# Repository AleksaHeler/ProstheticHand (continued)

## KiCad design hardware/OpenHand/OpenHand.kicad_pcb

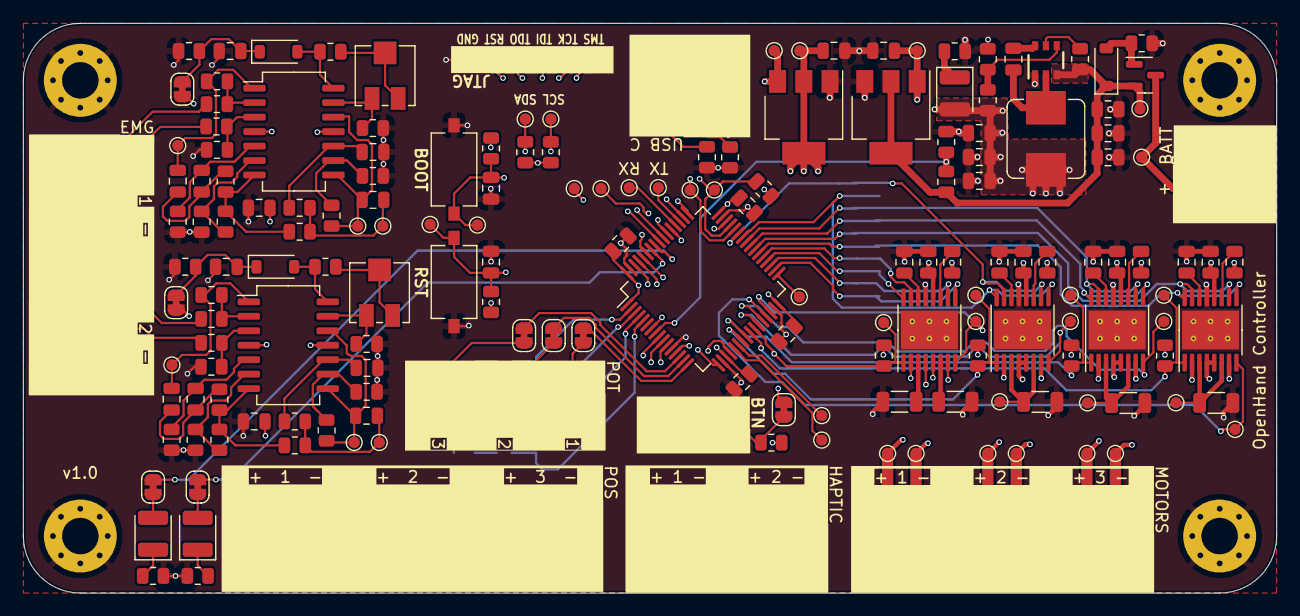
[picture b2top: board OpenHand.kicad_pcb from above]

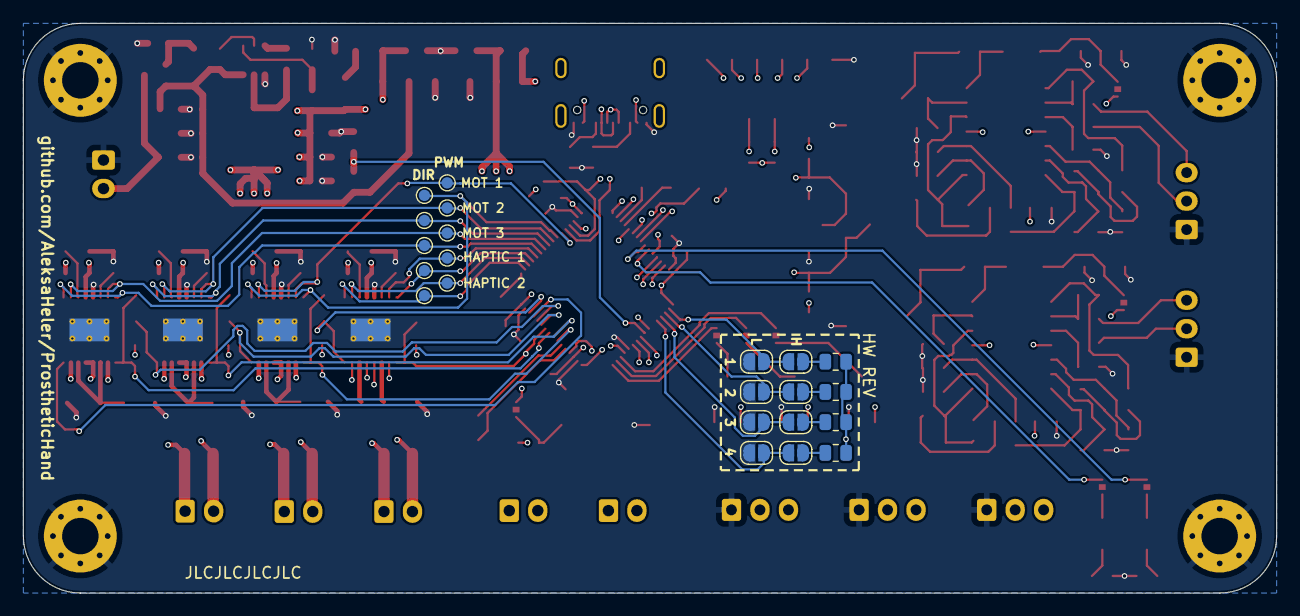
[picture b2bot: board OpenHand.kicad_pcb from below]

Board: 4 copper layers, 110.0 x 50.0 mm, 214 parts (22 on the bottom side), 135 nets.

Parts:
C1, C2, C3, C4, C5, C6, C9, C10, C16, C17: 100n; C_0805_2012Metric
C7, C8, C26, C27, C32, C33, C38, C39: 10u; C_0805_2012Metric
C11, C12, C14, C15: 22u; C_0805_2012Metric
C13: 1u; C_0805_2012Metric
C18, C19, C20, C21, C22, C23: 470n; C_0805_2012Metric
C24, C25: 330n; C_0805_2012Metric
C28, C29, C34, C35: 2u2; C_0805_2012Metric
C30, C31, C36, C37: 10n; C_0805_2012Metric
D1, D4: RED; LED_1210_3225Metric
D2: GREEN; LED_1210_3225Metric
D3: 5V Zener; D_SOD-123
D5, D6: SS14; D_SOD-123
H1, H2, H3, H4: M3_Hole; MountingHole_3.2mm_M3_Pad_Via
J1: CONN_MOTOR_1; JST_EH_S2B-EH_1x02_P2.50mm_Horizontal
J2: CONN_MOTOR_2; JST_EH_S2B-EH_1x02_P2.50mm_Horizontal
J3: CONN_BATT; JST_EH_S2B-EH_1x02_P2.50mm_Horizontal
J4: CONN_POS_1; JST_EH_S3B-EH_1x03_P2.50mm_Horizontal
J5: USB_C_CONN; USB_C_Receptacle_G-Switch_GT-USB-7010ASV
J6: CONN_MOTOR_3; JST_EH_S2B-EH_1x02_P2.50mm_Horizontal
J7: CONN_FDBK_1; JST_EH_S2B-EH_1x02_P2.50mm_Horizontal
J8: CONN_EMG_1; JST_EH_S3B-EH_1x03_P2.50mm_Horizontal
J9: CONN_POS_2; JST_EH_S3B-EH_1x03_P2.50mm_Horizontal
J10: CONN_FDBK_2; JST_EH_S2B-EH_1x02_P2.50mm_Horizontal
J11: CONN_EMG_2; JST_EH_S3B-EH_1x03_P2.50mm_Horizontal
J12: CONN_POS_3; JST_EH_S3B-EH_1x03_P2.50mm_Horizontal
JP1: JMPR_TRIM_1; SolderJumper-2_P1.3mm_Bridged_RoundedPad1.0x1.5mm
JP2: JMPR_LED_1; SolderJumper-2_P1.3mm_Bridged_RoundedPad1.0x1.5mm
JP3: JMPR_BTN_1; SolderJumper-2_P1.3mm_Bridged_RoundedPad1.0x1.5mm
JP4: JMPR_LED_2; SolderJumper-2_P1.3mm_Bridged_RoundedPad1.0x1.5mm
JP5: JMPR_TRIM_2; SolderJumper-2_P1.3mm_Bridged_RoundedPad1.0x1.5mm
JP6: JMPR_POT_1; SolderJumper-2_P1.3mm_Bridged_RoundedPad1.0x1.5mm
JP7, JP8, JP9, JP10, JP11, JP12, JP13, JP14: SolderJumper_2_Open; SolderJumper-2_P1.3mm_Open_RoundedPad1.0x1.5mm
JP15: JMPR_EMG_1_UC; SolderJumper-2_P1.3mm_Bridged_RoundedPad1.0x1.5mm
JP16: JMPR_EMG_2_UC; SolderJumper-2_P1.3mm_Bridged_RoundedPad1.0x1.5mm
L1: 3.3uH; L_Bourns_SRP7028A_7.3x6.6mm
Q1: AO3401A; SOT-23
R1, R5, R6, R7, R8, R12, R13, R14, R15, R16, R17, R21, R34, R37, R46, R47, R52, R53, R56, R57: 10k; R_0805_2012Metric
R2, R3: 5k1; R_0805_2012Metric
R4: 1.5k; R_0805_2012Metric
R9, R10, R20: 4k7; R_0805_2012Metric
R11, R19, R22, R24, R32, R35, R42, R43: 47k; R_0805_2012Metric
R18: 54.9k; R_0805_2012Metric
R23, R25, R33, R36: 15k; R_0805_2012Metric
R26, R27, R28, R29, R30, R31, R40, R41, R44, R45: 1k; R_0805_2012Metric
R38, R39, R48, R49, R50, R51: 18k; R_0805_2012Metric
R54, R55, R59: 0R2; R_1206_3216Metric
R58, R60: 4R7; R_1206_3216Metric
RV1: TRIM_POT_1; Potentiometer_Vishay_TS53YJ_Vertical
RV2: TRIM_POT_2; Potentiometer_Vishay_TS53YJ_Vertical
RV3: TRIM_POT_3; Potentiometer_Vishay_TS53YJ_Vertical
RV4, RV5: 100k; Potentiometer_Vishay_TS53YJ_Vertical
SW1: BTN_RST; SW_Tactile_SPST_NO_Straight_CK_PTS636Sx25SMTRLFS
SW2: BTN_BOOT; SW_Tactile_SPST_NO_Straight_CK_PTS636Sx25SMTRLFS
SW3: SW_Push; SW_Tactile_SPST_NO_Straight_CK_PTS636Sx25SMTRLFS
TP1: TP_BTN_RST; TestPoint_Pad_D1.0mm
TP2: TP_USB_D_P; TestPoint_Pad_D1.0mm
TP3: TP_USB_D_N; TestPoint_Pad_D1.0mm
TP4: TP_BTN_BOOT; TestPoint_Pad_D1.0mm
TP5: TP_JTAG_TMS; TestPoint_Pad_D1.0mm
TP6: TP_JTAG_TCK; TestPoint_Pad_D1.0mm
TP7: TP_JTAG_TDI; TestPoint_Pad_D1.0mm
TP8: TP_JTAG_TDO; TestPoint_Pad_D1.0mm
TP9: TP_JTAG_RST; TestPoint_Pad_D1.0mm
TP10: TP_JTAG_GND; TestPoint_Pad_D1.0mm
TP12: TP_UC_PIN_PA5; TestPoint_Pad_D1.0mm
TP13: TP_UC_PIN_PD2; TestPoint_Pad_D1.0mm
TP14: TP_UC_PIN_PA6; TestPoint_Pad_D1.0mm
TP18: TP_UC_TX; TestPoint_Pad_D1.0mm
TP19: TP_UC_RX; TestPoint_Pad_D1.0mm
TP20: TP_UC_PIN_PC12; TestPoint_Pad_D1.0mm
TP21: TP_UC_SCL; TestPoint_Pad_D1.0mm
TP22: TP_UC_SDA; TestPoint_Pad_D1.0mm
TP23: TP_UC_PIN_PB12; TestPoint_Pad_D1.0mm
TP24: TP_BATT_P; TestPoint_Pad_D1.0mm
TP25: TP_V_BATT; TestPoint_Pad_D1.0mm
TP26: TP_V_5V; TestPoint_Pad_D1.0mm
TP27: TP_V_3V3; TestPoint_Pad_D1.0mm
TP28: TP_V_N5V; TestPoint_Pad_D1.0mm
TP29: TP_EMG_1_AMP; TestPoint_Pad_D1.0mm
TP30: TP_EMG_2_AMP; TestPoint_Pad_D1.0mm
TP31: TP_EMG_1_HP; TestPoint_Pad_D1.0mm
TP32: TP_EMG_2_HP; TestPoint_Pad_D1.0mm
TP33: TP_EMG_1_LP; TestPoint_Pad_D1.0mm
TP34: TP_EMG_2_LP; TestPoint_Pad_D1.0mm
TP35: TP_MOT_1_EN; TestPoint_Pad_D1.0mm
TP36: TP_MOT_2_EN; TestPoint_Pad_D1.0mm
TP37: TP_MOT_1_IS; TestPoint_Pad_D1.0mm
TP38: TP_MOT_1_FAULT; TestPoint_Pad_D1.0mm
TP39: TP_MOT_2_IS; TestPoint_Pad_D1.0mm
TP40: TP_MOT_2_FAULT; TestPoint_Pad_D1.0mm
TP41: TP_MOT_1_UC1; TestPoint_Pad_D1.0mm
TP42: TP_MOT_2_UC1; TestPoint_Pad_D1.0mm
TP43: TP_MOT_1_UC2; TestPoint_Pad_D1.0mm
TP44: TP_MOT_2_UC2; TestPoint_Pad_D1.0mm
TP45: TP_MOT_1_OUT_P; TestPoint_Pad_D1.0mm
TP46: TP_MOT_2_OUT_P; TestPoint_Pad_D1.0mm
TP47: TP_MOT_1_OUT_N; TestPoint_Pad_D1.0mm
TP48: TP_MOT_2_OUT_N; TestPoint_Pad_D1.0mm
TP49: TP_MOT_3_EN; TestPoint_Pad_D1.0mm
TP50: TP_FDBK_MOT_EN; TestPoint_Pad_D1.0mm
TP51: TP_MOT_3_IS; TestPoint_Pad_D1.0mm
TP52: TP_MOT_3_FAULT; TestPoint_Pad_D1.0mm
TP53: TP_FDBK_MOT_FAULT; TestPoint_Pad_D1.0mm
TP54: TP_MOT_3_UC1; TestPoint_Pad_D1.0mm
TP55: TP_FDBK_MOT_1_UC1; TestPoint_Pad_D1.0mm
TP56: TP_MOT_3_UC2; TestPoint_Pad_D1.0mm
TP57: TP_FDBK_MOT_1_UC2; TestPoint_Pad_D1.0mm
TP58: TP_MOT_3_OUT_P; TestPoint_Pad_D1.0mm
TP59: TP_MOT_3_OUT_N; TestPoint_Pad_D1.0mm
TP60: TP_FDBK_MOT_2_UC1; TestPoint_Pad_D1.0mm
TP61: TP_FDBK_MOT_2_UC2; TestPoint_Pad_D1.0mm
U1: STM32F103RETx; LQFP-64_10x10mm_P0.5mm
U2: TPS565201DDCR; TPS565201DDCR_L
U3: AMS1117-3.3; SOT-223-3_TabPin2
U4: LT1175-5_SOT223; SOT-223-3_TabPin2
U5, U6: LM324; SO-14_5.3x10.2mm_P1.27mm
U7, U8, U9, U10: DRV8833PWP; HTSSOP-16-1EP_4.4x5mm_P0.65mm_EP3.4x5mm_Mask2.46x2.31mm_The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

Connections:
+3V3: C3.1, C4.1, C5.1, C6.1, C14.1, J4.3, J9.3, J12.3, R1.1, R4.2, R5.1, R6.2, R7.2, R8.1, R13.1, R14.1, R15.1, R16.1, RV1.3, RV2.3, RV3.3, TP27.1, U1.1 (VBAT), U1.13 (VDDA), U1.19 (VDD), U1.32 (VDD), U1.48 (VDD), U1.64 (VDD), U3.2 (VO)
+5V: C11.1, C12.1, C13.1, C16.1, C17.1, C30.1, C31.1, C32.1, C33.1, C36.1, C37.1, C38.1, C39.1, D4.2 (A), J5.A4 (VBUS), J5.A9 (VBUS), J5.B4 (VBUS), J5.B9 (VBUS), L1.2, R18.1, R52.2, R53.2, R56.2, R57.2, TP26.1, U3.3 (VI), U5.4 (V+), U6.4 (V+), U7.12 (VM), U8.12 (VM), U9.12 (VM), U10.12 (VM)
+BATT: C7.1, C8.1, C9.1, D3.1 (K), Q1.2 (S), R11.2, R17.2, TP25.1, U2.3 (VIN), U4.2 (IN)
-5V: C15.1, TP28.1, U4.1 (OUT), U5.11 (V-), U6.11 (V-)
/BATT_SENSE: R11.1, R12.2, U1.8 (PC0)
/Sensors/amp_out_1: C18.1, R32.2, TP29.1, U5.1
BAT_P: J3.2, Q1.3 (D), TP24.1
BTN_01: JP3.2 (B), U1.59 (PB7)
EMG_1_MIDPOINT: C22.1, R29.2, R40.1, TP31.1
EMG_01_N: J8.3, R28.2
EMG_01_P: J8.2, R26.2
EMG_01_UC: JP15.2 (B), U1.17 (PA3)
EMG_2_MIDPOINT: C23.1, R31.2, R41.1, TP32.1
EMG_02_N: J11.3, R30.2
EMG_02_P: J11.2, R27.2
EMG_02_UC: JP16.2 (B), U1.20 (PA4)
Earth: C1.2, C2.2, C3.2, C4.2, C5.2, C6.2, C7.2, C8.2, C9.2, C11.2, C12.2, C13.2, C14.2, C15.2, C16.2, C17.2, C24.1, C25.1, C26.2, C27.2, C28.1, C29.1, C32.2, C33.2, C34.1, C35.1, C38.2, C39.2, H1.1, H2.1, H3.1, H4.1, J3.1, J4.1, J5.A1 (GND), J5.A12 (GND), J5.B1 (GND), J5.B12 (GND), J8.1, J9.1, J11.1, J12.1, JP11.1 (A), JP12.1 (A), JP13.1 (A), JP14.1 (A), R2.2, R3.2, R9.2, R10.2, R12.1, R19.1, R20.2, R21.2, R22.1, R24.1, R33.2, R36.2, R38.2, R39.2, R44.2, R45.2, R48.2, R49.2, R50.2, R51.2, R54.1, R55.1, R58.1, R59.1, R60.1, RV1.1, RV2.1, RV3.1, SW1.2, SW2.2, SW3.2, TP10.1, U1.12 (VSSA), U1.18 (VSS), U1.31 (VSS), U1.47 (VSS), U1.63 (VSS), U2.1 (GND), U3.1 (GND), U4.3 (GND), U7.13 (GND), U7.17 (GND(PPAD)), U8.13 (GND), U8.17 (GND(PPAD)), U9.13 (GND), U9.17 (GND(PPAD)), U10.13 (GND), U10.17 (GND(PPAD))
HALL_SENS_01_S: J4.2, U1.9 (PC1)
HALL_SENS_02_S: J9.2, U1.10 (PC2)
HALL_SENS_03_S: J12.2, U1.11 (PC3)
HAPTIC_01_DIR: TP55.1, U1.36 (PB15), U10.16 (AIN1)
HAPTIC_01_N: J7.1, U10.4 (AOUT2)
HAPTIC_01_P: J7.2, U10.2 (AOUT1)
HAPTIC_01_PWM: TP57.1, U1.37 (PC6), U10.15 (AIN2)
HAPTIC_02_DIR: TP60.1, U1.34 (PB13), U10.9 (BIN1)
HAPTIC_02_N: J10.1, U10.5 (BOUT2)
HAPTIC_02_P: J10.2, U10.7 (BOUT1)
HAPTIC_02_PWM: TP61.1, U1.35 (PB14), U10.10 (BIN2)
HAPTIC_EN: R57.1, TP50.1, U1.26 (PB0), U10.1 (nSLEEP)
HAPTIC_FAULT: TP53.1, U1.30 (PB11), U10.8 (nFAULT)
HW_REV_01: JP7.1 (A), JP11.2 (B), U1.2 (PC13)
HW_REV_02: JP8.1 (A), JP12.2 (B), U1.3 (PC14)
HW_REV_03: JP9.1 (A), JP13.2 (B), U1.4 (PC15)
HW_REV_04: JP10.1 (A), JP14.2 (B), U1.5 (PD0)
JTAG_RST: TP9.1, U1.56 (PB4)
JTAG_TCK: TP6.1, U1.49 (PA14)
JTAG_TDI: TP7.1, U1.50 (PA15)
JTAG_TDO: TP8.1, U1.55 (PB3)
JTAG_TMS: TP5.1, U1.46 (PA13)
LED_1: JP2.2 (B), U1.57 (PB5)
LED_2: JP4.2 (B), U1.58 (PB6)
MOTOR_01_DIR: TP41.1, U1.42 (PA9), U7.9 (BIN1), U7.16 (AIN1)
MOTOR_01_EN: R52.1, TP35.1, U1.23 (PA7), U7.1 (nSLEEP)
MOTOR_01_FAULT: TP38.1, U1.27 (PB1), U7.8 (nFAULT)
MOTOR_01_N: J1.1, TP47.1, U7.4 (AOUT2), U7.5 (BOUT2)
MOTOR_01_P: J1.2, TP45.1, U7.2 (AOUT1), U7.7 (BOUT1)
MOTOR_01_PWM: TP43.1, U1.43 (PA10), U7.10 (BIN2), U7.15 (AIN2)
MOTOR_02_DIR: TP42.1, U1.40 (PC9), U8.9 (BIN1), U8.16 (AIN1)
MOTOR_02_EN: R53.1, TP36.1, U1.24 (PC4), U8.1 (nSLEEP)
MOTOR_02_FAULT: TP40.1, U1.28 (PB2), U8.8 (nFAULT)
MOTOR_02_N: J2.1, TP48.1, U8.4 (AOUT2), U8.5 (BOUT2)
MOTOR_02_P: J2.2, TP46.1, U8.2 (AOUT1), U8.7 (BOUT1)
MOTOR_02_PWM: TP44.1, U1.41 (PA8), U8.10 (BIN2), U8.15 (AIN2)
MOTOR_03_DIR: TP54.1, U1.38 (PC7), U9.9 (BIN1), U9.16 (AIN1)
MOTOR_03_EN: R56.1, TP49.1, U1.25 (PC5), U9.1 (nSLEEP)
MOTOR_03_FAULT: TP52.1, U1.29 (PB10), U9.8 (nFAULT)
MOTOR_03_N: J6.1, TP59.1, U9.4 (AOUT2), U9.5 (BOUT2)
MOTOR_03_P: J6.2, TP58.1, U9.2 (AOUT1), U9.7 (BOUT1)
MOTOR_03_PWM: TP56.1, U1.39 (PC8), U9.10 (BIN2), U9.15 (AIN2)
unnamed: C18.2, C19.1, R23.1
unnamed: C20.1, R35.2, TP30.1, U6.1
unnamed: C20.2, C21.1, R25.1
unnamed: D1.2 (A), JP2.1 (A)
unnamed: D1.1 (K), R9.1
unnamed: D2.2 (A), JP4.1 (A)
unnamed: D2.1 (K), R10.1
unnamed: D3.2 (A), Q1.1 (G), R19.2
unnamed: D4.1 (K), R20.1
unnamed: D5.2 (A), R43.1, U5.14
unnamed: C26.1, D5.1 (K), JP15.1 (A), R48.1
unnamed: D6.2 (A), R42.1, U6.14
unnamed: C27.1, D6.1 (K), JP16.1 (A), R51.1
unnamed: J5.A5 (CC1), R2.1
unnamed: J5.B5 (CC2), R3.1
unnamed: JP1.1 (A), RV1.2
unnamed: JP3.1 (A), R8.2, SW3.1
unnamed: JP5.1 (A), RV2.2
unnamed: JP6.1 (A), RV3.2
unnamed: JP7.2 (B), R13.2
unnamed: JP8.2 (B), R14.2
unnamed: JP9.2 (B), R15.2
unnamed: JP10.2 (B), R16.2
unnamed: R23.2, R29.1, R34.2, U5.7
unnamed: R25.2, R31.1, R37.2, U6.7
unnamed: R42.2, RV5.1, RV5.2
unnamed: R43.2, RV4.1, RV4.2
unnamed: TP12.1, U1.21 (PA5)
unnamed: TP14.1, U1.22 (PA6)
unnamed: TP23.1, U1.33 (PB12)
unnamed: TP20.1, U1.53 (PC12)
unnamed: TP13.1, U1.54 (PD2)
unnamed: R17.1, U2.5 (EN)
unnamed: C10.1, L1.1, U2.2 (SW)
unnamed: C10.2, U2.6 (VBST)
unnamed: R18.2, R21.1, U2.4 (VFB)
unnamed: R22.2, R26.1, U5.3 (+)
unnamed: R28.1, R32.1, U5.2 (-)
unnamed: C19.2, R33.1, U5.5 (+)
unnamed: R34.1, R38.1, U5.6 (-)
unnamed: C24.2, R40.2, U5.10 (+)
unnamed: R46.1, R49.1, U5.9 (-)
unnamed: C22.2, R46.2, TP33.1, U5.8, U5.12 (+)
unnamed: R44.1, RV4.3, U5.13 (-)
unnamed: R24.2, R27.1, U6.3 (+)
unnamed: R30.1, R35.1, U6.2 (-)
unnamed: C21.2, R36.1, U6.5 (+)
unnamed: R37.1, R39.1, U6.6 (-)
unnamed: C25.2, R41.2, U6.10 (+)
unnamed: R47.1, R50.1, U6.9 (-)
unnamed: C23.2, R47.2, TP34.1, U6.8, U6.12 (+)
unnamed: R45.1, RV5.3, U6.13 (-)
unnamed: R54.2, TP37.1, U7.3 (AISEN), U7.6 (BISEN)
unnamed: C30.2, U7.11 (VCP)
unnamed: C28.2, U7.14 (VINT)
unnamed: R55.2, TP39.1, U8.3 (AISEN), U8.6 (BISEN)
unnamed: C31.2, U8.11 (VCP)
unnamed: C29.2, U8.14 (VINT)
unnamed: R59.2, TP51.1, U9.3 (AISEN), U9.6 (BISEN)
unnamed: C36.2, U9.11 (VCP)
unnamed: C34.2, U9.14 (VINT)
unnamed: R58.2, U10.3 (AISEN)
unnamed: R60.2, U10.6 (BISEN)
unnamed: C37.2, U10.11 (VCP)
unnamed: C35.2, U10.14 (VINT)
TRIM_POT_01: JP1.2 (B), U1.16 (PA2)
TRIM_POT_02: JP5.2 (B), U1.15 (PA1)
TRIM_POT_03: JP6.2 (B), U1.14 (PA0)
UC_BOOT: C2.1, R5.2, SW2.1, TP4.1, U1.60 (BOOT0)
UC_RST: C1.1, R1.2, SW1.1, TP1.1, U1.7 (NRST)
UC_RX: TP19.1, U1.52 (PC11)
UC_SCL: R7.1, TP21.1, U1.61 (PB8)
UC_SDA: R6.1, TP22.1, U1.62 (PB9)
UC_TX: TP18.1, U1.51 (PC10)
USB_D+: J5.A7 (D-), J5.B7 (D-), R4.1, TP2.1, U1.45 (PA12)
USB_D-: J5.A6 (D+), J5.B6 (D+), TP3.1, U1.44 (PA11)

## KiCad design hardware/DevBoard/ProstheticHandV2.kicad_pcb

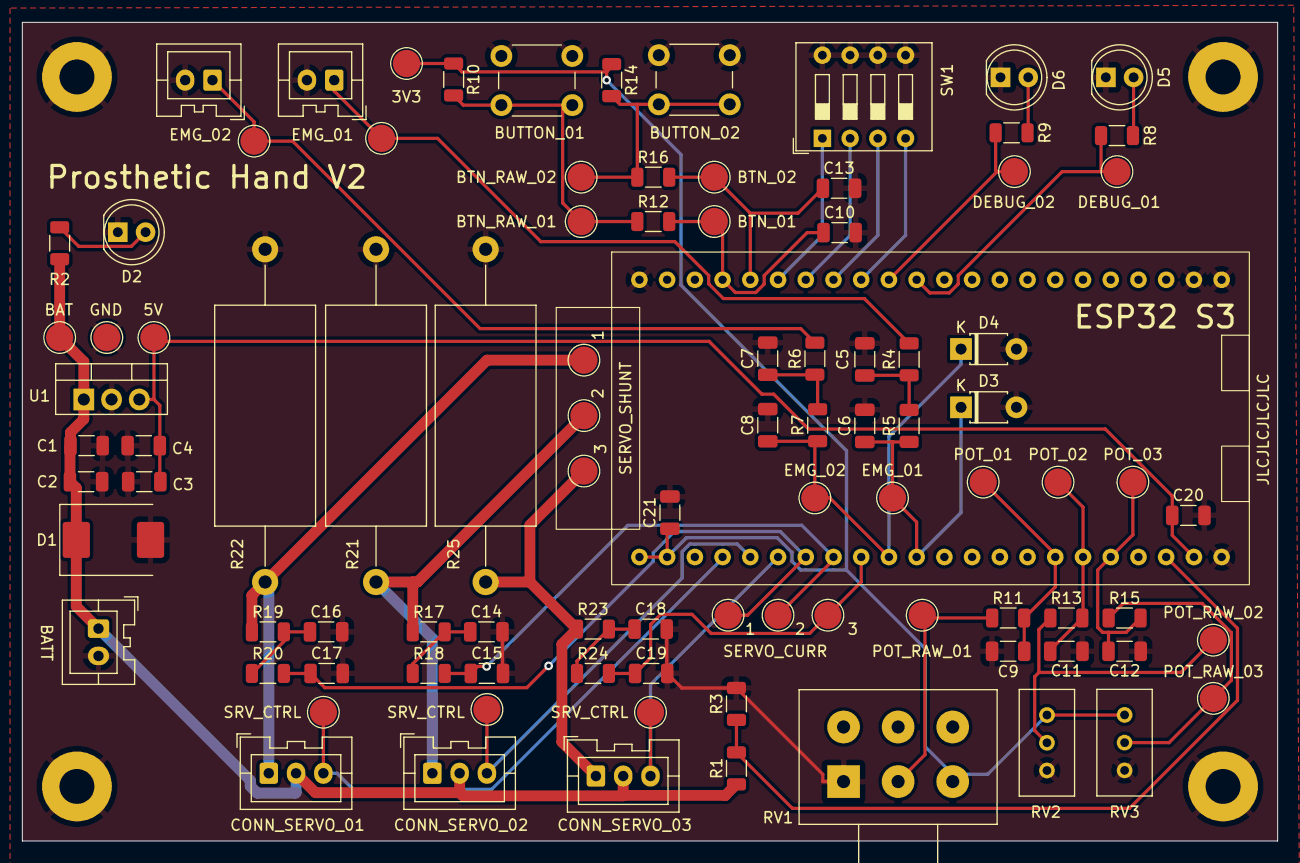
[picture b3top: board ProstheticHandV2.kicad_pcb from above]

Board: 2 copper layers, 115.0 x 75.0 mm, 99 parts (0 on the bottom side), 42 nets.

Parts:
A1: ESP32S3_DevModule
C1, C3, C5, C6, C7, C8: 1uF; C_1206_3216Metric
C2, C4, C9, C10, C11, C12, C13, C20, C21: 0.1uF; C_1206_3216Metric
C14, C15, C16, C17, C18, C19: 100nF; C_1206_3216Metric
D1: SK36; D_SMC
D2: LED GREEN; LED_D5.0mm
D3, D4: 5v1; D_T-1_P5.08mm_Horizontal
D5: LED RED; LED_D5.0mm
D6: LED BLUE; LED_D5.0mm
H1, H2, H3, H4: MountingHole_Pad; MountingHole_3.2mm_M3_Pad
J1: BATT_CONNECTOR; JST_XA_B02B-XASK-1_1x02_P2.50mm_Vertical
J2: EMG_SENSOR_01; JST_XA_B02B-XASK-1_1x02_P2.50mm_Vertical
J3: EMG_SENSOR_02; JST_XA_B02B-XASK-1_1x02_P2.50mm_Vertical
J4: CONN_SERVO_02; JST_XA_B03B-XASK-1_1x03_P2.50mm_Vertical
J5: CONN_SERVO_01; JST_XA_B03B-XASK-1_1x03_P2.50mm_Vertical
J6: CONN_SERVO_03; JST_XA_B03B-XASK-1_1x03_P2.50mm_Vertical
R1: 4k7; R_1206_3216Metric
R2, R4, R5, R6, R7, R10, R11, R12, R13, R14, R15, R16: 10k; R_1206_3216Metric
R3, R17, R18, R19, R20, R23, R24: 1k; R_1206_3216Metric
R8, R9: 220; R_1206_3216Metric
R21, R22, R25: 0.1; R_Axial_DIN0922_L20.0mm_D9.0mm_P30.48mm_Horizontal
RV1: Pot. 5k; Potentiometer_Alps_RK163_Dual_Horizontal
RV2, RV3: Trim Pot. 10k; Potentiometer_Bourns_3296W_Vertical
SW1: DIP_SWITCH; SW_DIP_SPSTx04_Slide_9.78x12.34mm_W7.62mm_P2.54mm
SW2: BUTTON_01; SW_PUSH_6mm_H5mm
SW3: BUTTON_02; SW_PUSH_6mm_H5mm
TP1: TP_BATT; TestPoint_Pad_D2.5mm
TP2: TP_5V_REG; TestPoint_Pad_D2.5mm
TP3: TP_GND; TestPoint_Pad_D2.5mm
TP4: TP_EMG_01_IN; TestPoint_Pad_D2.5mm
TP5: TP_EMG_01_UC; TestPoint_Pad_D2.5mm
TP6: TP_EMG_02_IN; TestPoint_Pad_D2.5mm
TP7: TP_EMG_02_UC; TestPoint_Pad_D2.5mm
TP8: TP_DEBUG_01; TestPoint_Pad_D2.5mm
TP9: TP_DEBUG_02; TestPoint_Pad_D2.5mm
TP10: TP_3v3; TestPoint_Pad_D2.5mm
TP11: TP_POT_RAW_01; TestPoint_Pad_D2.5mm
TP12: TP_POT_01; TestPoint_Pad_D2.5mm
TP13: TP_BTN_RAW_01; TestPoint_Pad_D2.5mm
TP14: TP_BTN_01; TestPoint_Pad_D2.5mm
TP15: TP_POT_RAW_02; TestPoint_Pad_D2.5mm
TP16: TP_POT_02; TestPoint_Pad_D2.5mm
TP17: TP_POT_RAW_03; TestPoint_Pad_D2.5mm
TP18: TP_POT_03; TestPoint_Pad_D2.5mm
TP19: TP_BTN_RAW_02; TestPoint_Pad_D2.5mm
TP20: TP_BTN_02; TestPoint_Pad_D2.5mm
TP21: TP_SERVO_CONTROL_02; TestPoint_Pad_D2.5mm
TP22: TP_SERVO_CONTROL_01; TestPoint_Pad_D2.5mm
TP23: TP_SERVO_CURR_RAW_02; TestPoint_Pad_D2.5mm
TP24: TP_SERVO_CURR_02; TestPoint_Pad_D2.5mm
TP25: TP_SERVO_CURR_RAW_01; TestPoint_Pad_D2.5mm
TP26: TP_SERVO_CURR_01; TestPoint_Pad_D2.5mm
TP27: TP_SERVO_CONTROL_03; TestPoint_Pad_D2.5mm
TP28: TP_SERVO_CURR_RAW_03; TestPoint_Pad_D2.5mm
TP29: TP_SERVO_CURR_03; TestPoint_Pad_D2.5mm
U1: LM7805_TO220; TO-220-3_Vertical

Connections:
+3V3: A1.1 (3v3), A1.2 (3v3), C21.1, R10.1, R14.1, RV1.3, RV2.3, RV3.3, TP10.1
+5V: A1.21 (5v), C3.1, C4.1, C20.1, TP2.1, U1.3 (VO)
+BATT: C1.1, C2.1, D1.1 (K), J1.1, J4.2, J5.2, J6.2, R1.1, R2.1, TP1.1, U1.1 (VI)
BATT_SENSE: A1.20 (14), R1.2, R3.1
BUTTON_01: A1.41 (1), C10.1, R12.2, TP14.1
BUTTON_02: A1.40 (2), C13.1, R16.2, TP20.1
DEBUG_LED_01: A1.34 (37), R8.1, TP8.1
DEBUG_LED_02: A1.35 (38), R9.2, TP9.1
DIP_SWITCH_00: A1.39 (42), SW1.1
DIP_SWITCH_01: A1.38 (41), SW1.2
DIP_SWITCH_02: A1.37 (40), SW1.3
DIP_SWITCH_03: A1.36 (39), SW1.4
EMG_SENSOR_01: A1.11 (18), C6.1, D3.1 (K), R5.1, TP5.1
EMG_SENSOR_02: A1.10 (17), C8.1, D4.1 (K), R7.1, TP7.1
GND: A1.22 (GND), A1.23 (GND), A1.24 (GND), A1.44 (GND), C1.2, C2.2, C3.2, C4.2, C5.2, C6.2, C7.2, C8.2, C9.2, C10.2, C11.2, C12.2, C13.2, C14.2, C15.2, C16.2, C17.2, C18.2, C19.2, C20.2, C21.2, D1.2 (A), D2.1 (K), D3.2 (A), D4.2 (A), D5.1 (K), D6.1 (K), H1.1, H2.1, H3.1, H4.1, J1.2, J2.2, J3.2, R3.2, R21.2, R22.2, R25.2, RV1.1, RV2.1, RV3.1, SW1.5, SW1.6, SW1.7, SW1.8, SW2.1, SW3.1, TP3.1, U1.2 (GND)
unnamed: C5.1, R4.1, R5.2
unnamed: C7.1, R6.1, R7.2
unnamed: C14.1, R17.2, R18.1
unnamed: C16.1, R19.2, R20.1
unnamed: C18.1, R23.2, R24.1
unnamed: D2.2 (A), R2.2
unnamed: D5.2 (A), R8.2
unnamed: D6.2 (A), R9.1
unnamed: J2.1, R4.2, TP4.1
unnamed: J3.1, R6.2, TP6.1
unnamed: J4.1, R17.1, R21.1, TP23.1
unnamed: J5.1, R19.1, R22.1, TP25.1
unnamed: J6.1, R23.1, R25.1, TP28.1
unnamed: R10.2, R12.1, SW2.2, TP13.1
unnamed: R11.1, RV1.2, TP11.1
unnamed: R13.1, RV2.2, TP15.1
unnamed: R14.2, R16.1, SW3.2, TP19.1
unnamed: R15.1, RV3.2, TP17.1
POT_01: A1.16 (10), C9.1, R11.2, TP12.1
POT_02: A1.17 (11), C11.1, R13.2, TP16.1
POT_03: A1.18 (12), C12.1, R15.2, TP18.1
SERVO_CONTROL_01: A1.4, J5.3, TP22.1
SERVO_CONTROL_02: A1.5, J4.3, TP21.1
SERVO_CONTROL_03: A1.6, J6.3, TP27.1
SERVO_CURR_01: A1.7, C17.1, R20.2, TP26.1
SERVO_CURR_02: A1.8 (15), C15.1, R18.2, TP24.1
SERVO_CURR_03: A1.9 (16), C19.1, R24.2, TP29.1

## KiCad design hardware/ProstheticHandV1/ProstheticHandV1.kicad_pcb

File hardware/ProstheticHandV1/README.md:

# PCB & HW designs of the prosthetic hand project

For designing those we use [KiCAD](https://www.kicad.org/download/). Good tutorial can be found [here](https://www.youtube.com/playlist?list=PL3bNyZYHcRSUhUXUt51W6nKvxx2ORvUQB). Although it's for a bit older version of the KiCAD it is still usefull.

For now only two project are here:
 - **DevelopmentBoard** - First example board to test the KiCAD software and to try our hand at making our own PCB at home (TODO: update this document with findings once home-made pcb is done)
 - **ProstheticHand v1** - The actual PCB design that will be used in the prosthetic hand (for the first prototype), hopefully to be ordered from PCB manufacturer

Folders:
 - **images** - contains images of the PCBs and hardware
 - **libraries** - contains libraries used in KiCAD

Versioning:
 - v1.x -> first prototype, with v1.0 being the first design, and then iterating trough v1.1, v1.2...
 - v2.x -> todo

## Development Board

Here is the schematic of the development board:

It contains 4 buttons (with pullup resistors), 3 potentiometers (two trim pots, and one guitar pot), two servo connectors, JTAG connector and 12V barrel jack.

Here are some PCB screenshots:

And some photos of the protoboard build:

## Prosthetic Hand v1

We're using EPS32-S3:
 - https://api.riot-os.org/group__cpu__esp32__esp32s3.html

Components ideas for this iteration of the board:
 - debug LED
 - 2x pot
 - oled display
 - 2x buttons
 - 4x servos
 - current shunts for servo current measurement (we have 1 ohm power resistors at hand)
 - battery voltage sensing (connected to a battery -> 4 cell Li-ion)
 - [LDO voltage regulator](https://en.wikipedia.org/wiki/Low-dropout_regulator)
 - JTAG for programming and debugging
 - external power connector (selectable between this power input or the batteries by a switch)
 - two EMG sensor input pins (simple analog read)

Used ESP32 GPIO pins:
 - Servo output -> GPIO04, GPIO05, GPIO26, GPIO27 
 - Servo current sensing -> GPIO34, GPIO35, GPIO36, GPIO39
 - Debug LED -> GPIO23
 - JTAG -> GPIO12, GPIO13, GPIO14, GPIO15
 - UART -> GPIO01, GPIO03 (using built in serial to usb chip, no our connnected hardware)
 - Buttons -> GPIO18, GPIO19
 - Pots -> GPIO32, GPIO33
 - Battery voltage -> GPIO25
 - OLED display SPI com -> GPIO21, GPIO22
 - two EMG sensor input pins (simple analog read) -> 

Maybe: selectable pin functions using DIP swithces or jumper header connectors (we had some 4x DIP switches at hand so we're using them): each pin can be routed to some functionality by enabling these DIP switches. For example we can use a pin as a button input or as a pot input based on the DIP swith configuration. This is purely hardware oriented configuration and we have to then configure the code to support these changes.

## Prosthetic Hand v2

Ideas:
- 3 servo motors, current sensing for each and MOSFET to control the power/current they get
- MOSFETs controlled by op-amps, where uC gives them using PWM signal and sets the max current
- (test if PWM to DC voltage works, test if given DC voltage by uC works with op-ampto set max current) 
- 2 debug LEDs (one main RED LED, one green LED for sensor actuating)
- 5V dropdown regulator
- battery voltage sensing
- 3 potentiometers (one big, two trim pots)
- 2 buttons
- 4 dip switches for configuration
- 2 sensor connections
- sensors will be on a separate board with 2x 9V batteries
- check if we can have OLED connected to display data or just use JSON format over serial monitor and Processing
- still use full-size ESP32 S3 Devkit C boards

KiCad 7 ESP32 PCB Design Full Tutorial: https://www.youtube.com/watch?v=b-7bMl6fJio
RF + MCU PCB Design Review: https://www.youtube.com/watch?v=71bW_sKZIZw

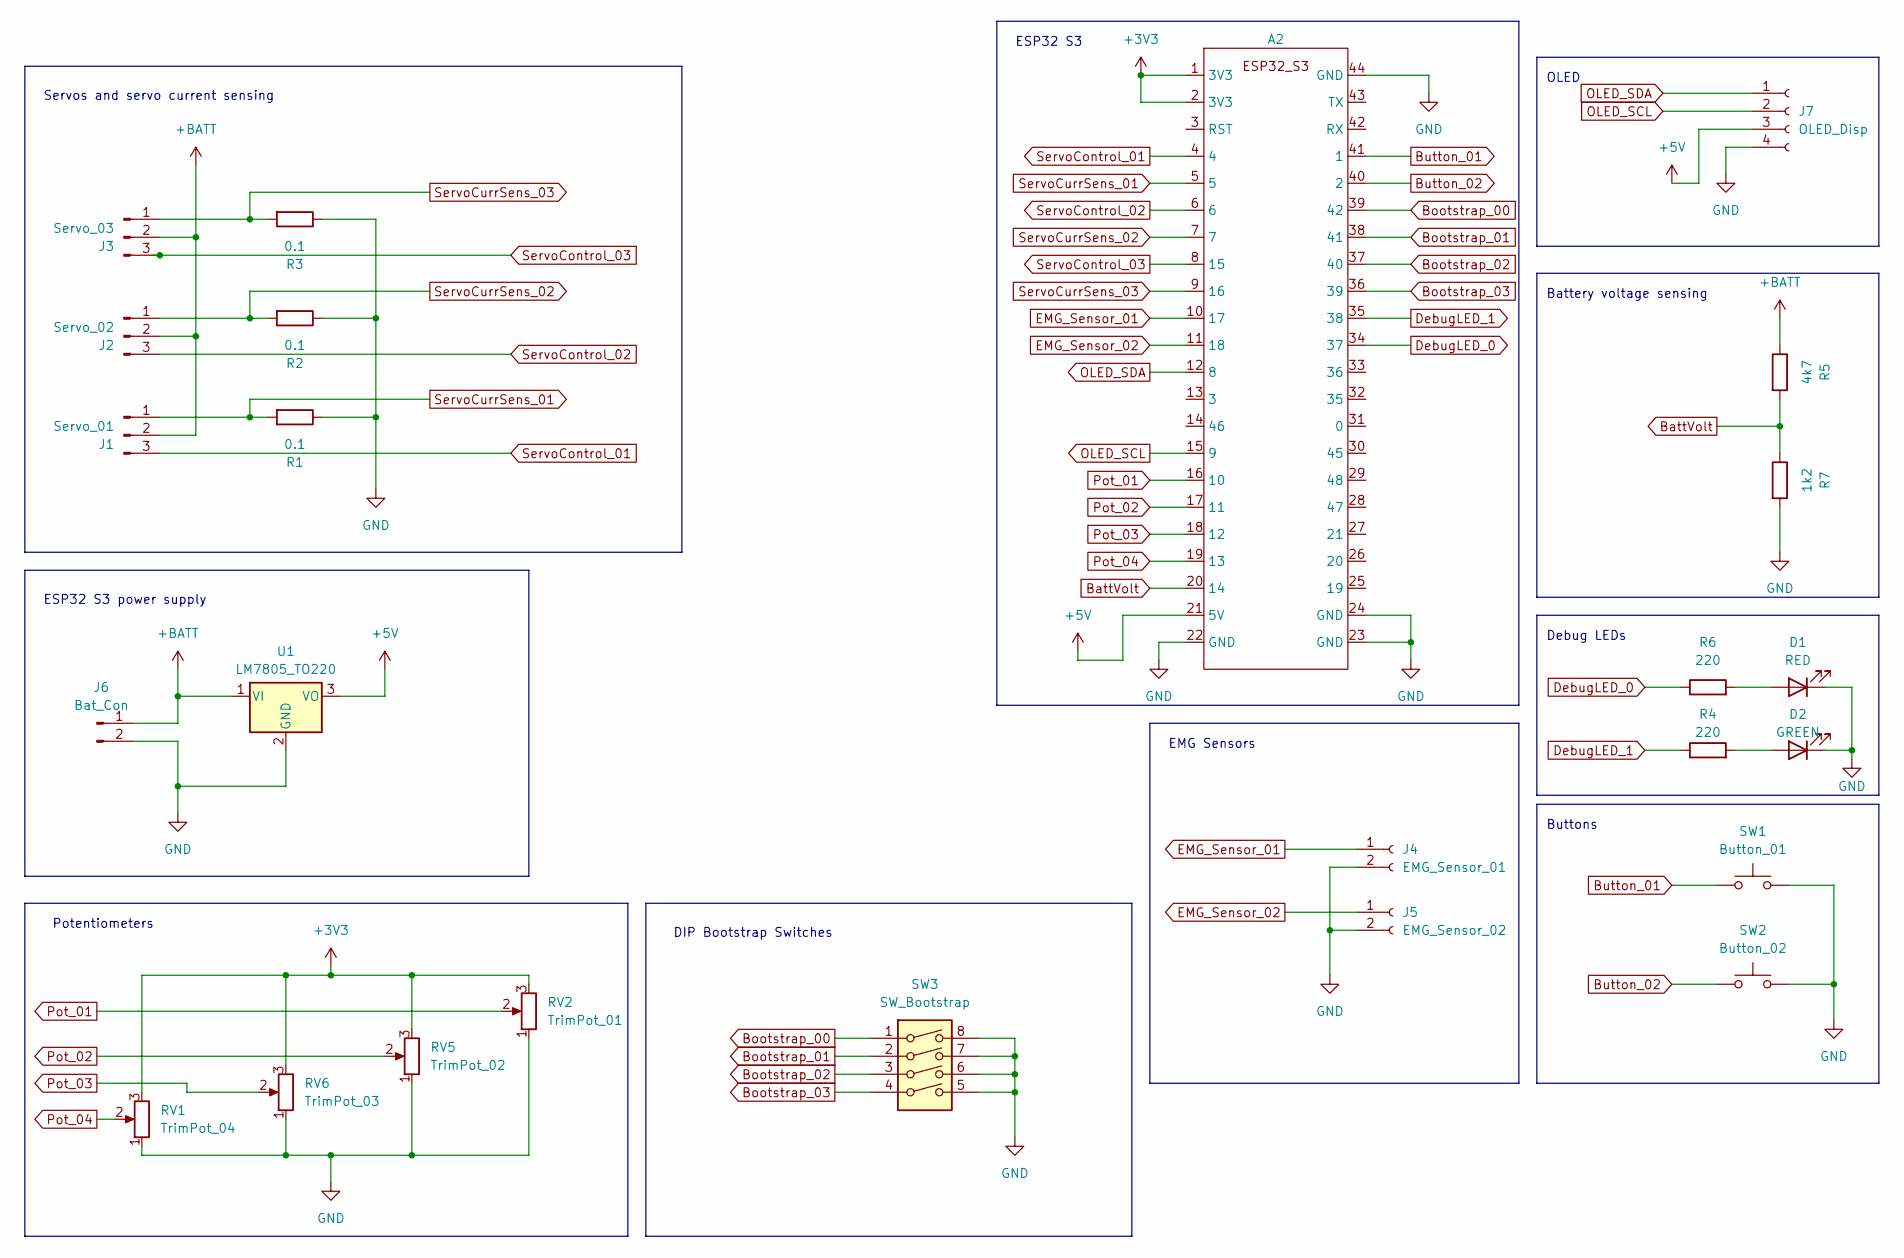
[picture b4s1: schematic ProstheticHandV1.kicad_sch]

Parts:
A2: ESP32S3_DevModule
D1: RED; LED_D5.0mm
D2: GREEN; LED_D5.0mm
J1: Servo_01; PinHeader_1x03_P2.54mm_Vertical
J2: Servo_02; PinHeader_1x03_P2.54mm_Vertical
J3: Servo_03; PinHeader_1x03_P2.54mm_Vertical
J4: EMG_Sensor_01; PinSocket_1x02_P2.54mm_Vertical
J5: EMG_Sensor_02; PinSocket_1x02_P2.54mm_Vertical
J6: Bat_Con; PinHeader_1x02_P2.54mm_Vertical
J7: OLED_Disp; PinHeader_1x04_P2.54mm_Vertical
R1, R2, R3: 0.1; R_Axial_Power_L25.0mm_W9.0mm_P27.94mm
R4, R6: 220; R_Axial_DIN0207_L6.3mm_D2.5mm_P7.62mm_Horizontal
R5: 4k7; R_Axial_DIN0207_L6.3mm_D2.5mm_P7.62mm_Horizontal
R7: 1k2; R_Axial_DIN0207_L6.3mm_D2.5mm_P7.62mm_Horizontal
RV1: TrimPot_04; PinHeader_1x03_P2.54mm_Vertical
RV2: TrimPot_01; Potentiometer_Alps_RK163_Single_Horizontal
RV5: TrimPot_02; Potentiometer_Alps_RK163_Single_Horizontal
RV6: TrimPot_03; PinHeader_1x03_P2.54mm_Vertical
SW1: Button_01; SW_PUSH_6mm
SW2: Button_02; SW_PUSH_6mm
SW3: SW_Bootstrap; SW_DIP_SPSTx04_Slide_9.78x12.34mm_W7.62mm_P2.54mm
U1: LM7805_TO220; TO-220-3_Vertical

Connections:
+3V3: A2.1 (3V3), A2.2 (3V3), RV1.3, RV2.3, RV5.3, RV6.3
+5V: A2.21 (5V), J7.3, U1.3 (VO)
+BATT: J1.2, J2.2, J3.2, J6.1, R5.1, U1.1 (VI)
BattVolt: A2.20 (14), R5.2, R7.1
Bootstrap_00: A2.39 (42), SW3.1
Bootstrap_01: A2.38 (41), SW3.2
Bootstrap_02: A2.37 (40), SW3.3
Bootstrap_03: A2.36 (39), SW3.4
Button_01: A2.41 (1), SW1.1
Button_02: A2.40 (2), SW2.1
DebugLED_0: A2.34 (37), R6.1
DebugLED_1: A2.35 (38), R4.1
EMG_Sensor_01: A2.10 (17), J4.1
EMG_Sensor_02: A2.11 (18), J5.1
GND: A2.22 (GND), A2.23 (GND), A2.24 (GND), A2.44 (GND), D1.1 (K), D2.1 (K), J4.2, J5.2, J6.2, J7.4, R1.1, R2.1, R3.1, R7.2, RV1.1, RV2.1, RV5.1, RV6.1, SW1.2, SW2.2, SW3.5, SW3.6, SW3.7, SW3.8, U1.2 (GND)
unnamed: D1.2 (A), R6.2
unnamed: D2.2 (A), R4.2
OLED_SCL: A2.15 (9), J7.2
OLED_SDA: A2.12 (8), J7.1
Pot_01: A2.16 (10), RV2.2
Pot_02: A2.17 (11), RV5.2
Pot_03: A2.18 (12), RV6.2
Pot_04: A2.19 (13), RV1.2
ServoControl_01: A2.4, J1.3
ServoControl_02: A2.6, J2.3
ServoControl_03: A2.8 (15), J3.3
ServoCurrSens_01: A2.5, J1.1, R1.2
ServoCurrSens_02: A2.7, J2.1, R2.2
ServoCurrSens_03: A2.9 (16), J3.1, R3.2

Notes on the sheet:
Servos and servo current sensing
DIP Bootstrap Switches
EMG Sensors
OLED
ESP32 S3 power supply
Buttons
Battery voltage sensing
Potentiometers
ESP32 S3
Debug LEDs

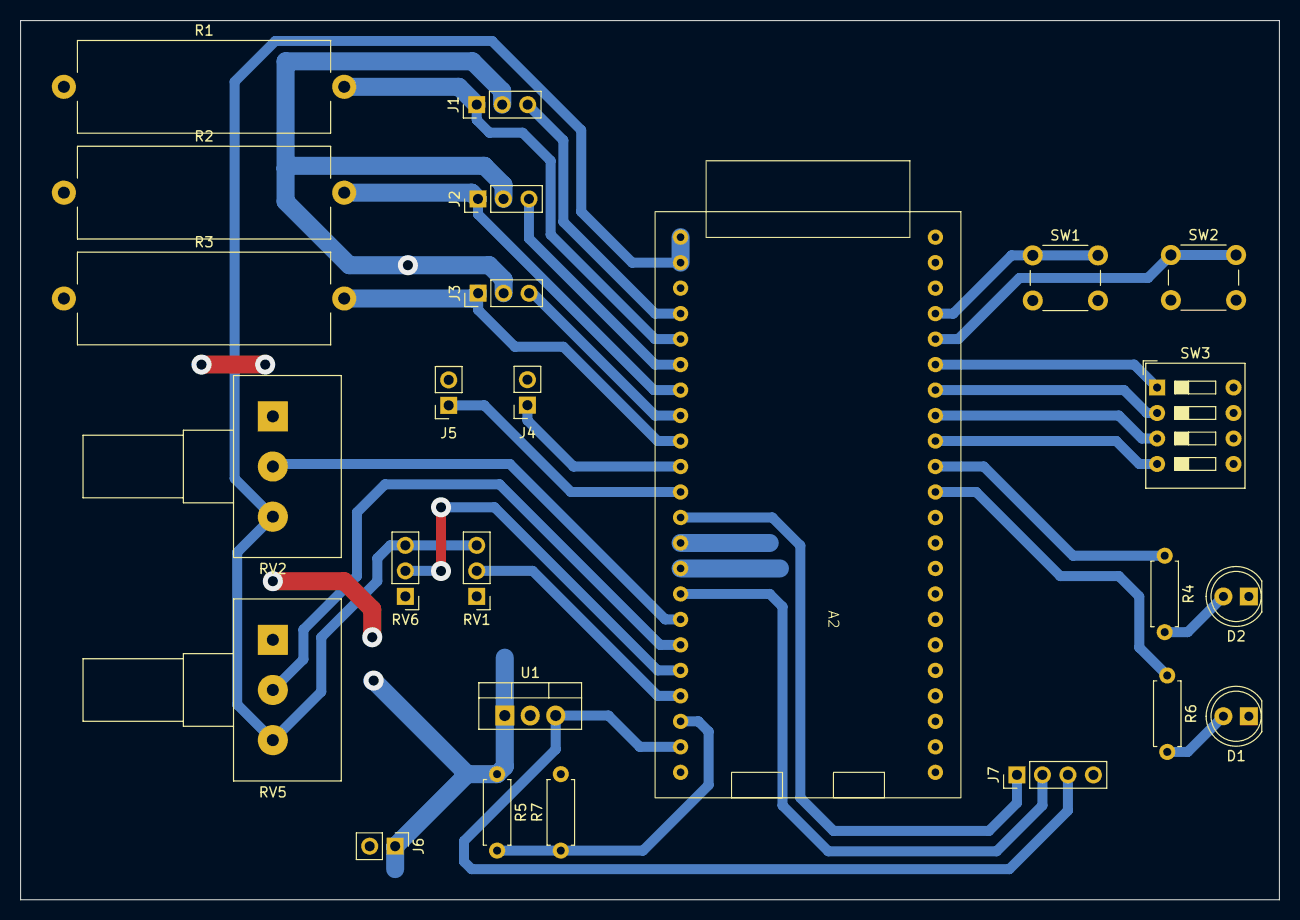
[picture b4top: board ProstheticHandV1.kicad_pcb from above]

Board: 2 copper layers, 125.5 x 87.6 mm, 25 parts (0 on the bottom side), 29 nets.

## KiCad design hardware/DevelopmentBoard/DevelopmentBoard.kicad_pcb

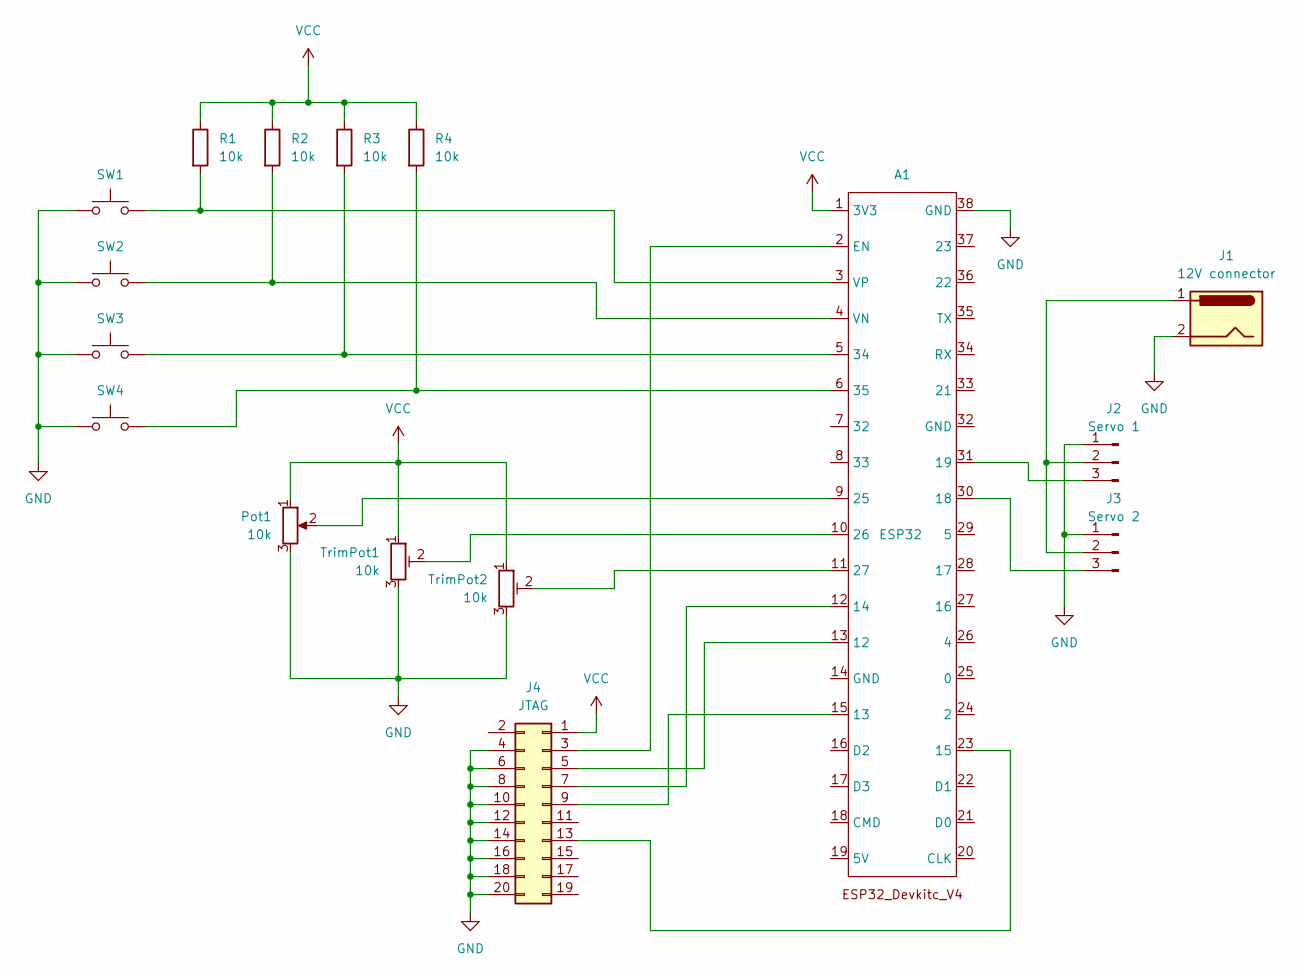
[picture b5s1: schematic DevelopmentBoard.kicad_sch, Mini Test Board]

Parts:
A1: ESP32; ICM_ESP32_DevKitC_V4
J1: 12V connector; BarrelJack_Horizontal
J2: Servo 1; PinHeader_1x03_P2.54mm_Vertical
J3: Servo 2; PinHeader_1x03_P2.54mm_Vertical
J4: JTAG; PinHeader_2x10_P2.54mm_Vertical
Pot1: 10k; Potentiometer_Piher_T-16H_Single_Horizontal
R1, R2, R3, R4: 10k; R_Axial_DIN0207_L6.3mm_D2.5mm_P7.62mm_Horizontal
SW1, SW2, SW3, SW4: SW_Push; SW_PUSH_6mm
TrimPot1, TrimPot2: 10k; Potentiometer_Bourns_3386C_Horizontal

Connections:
GND: A1.38 (GND), J1.2, J2.1, J3.1, J4.4, J4.6, J4.8, J4.10, J4.12, J4.14, J4.16, J4.18, J4.20, Pot1.3, SW1.1, SW2.1, SW3.1, SW4.1, TrimPot1.3, TrimPot2.3
unnamed: A1.13 (12), J4.5
unnamed: A1.15 (13), J4.9
unnamed: A1.12 (14), J4.7
unnamed: A1.23 (15), J4.13
unnamed: A1.30 (18), J3.3
unnamed: A1.31 (19), J2.3
unnamed: A1.9 (25), Pot1.2
unnamed: A1.10 (26), TrimPot1.2
unnamed: A1.11 (27), TrimPot2.2
unnamed: A1.5 (34), R3.2, SW3.2
unnamed: A1.6 (35), R4.2, SW4.2
unnamed: A1.2 (EN), J4.3
unnamed: A1.4 (VN), R2.2, SW2.2
unnamed: A1.3 (VP), R1.2, SW1.2
unnamed: J1.1, J2.2, J3.2
VCC: A1.1 (3V3), J4.1, Pot1.1, R1.1, R2.1, R3.1, R4.1, TrimPot1.1, TrimPot2.1

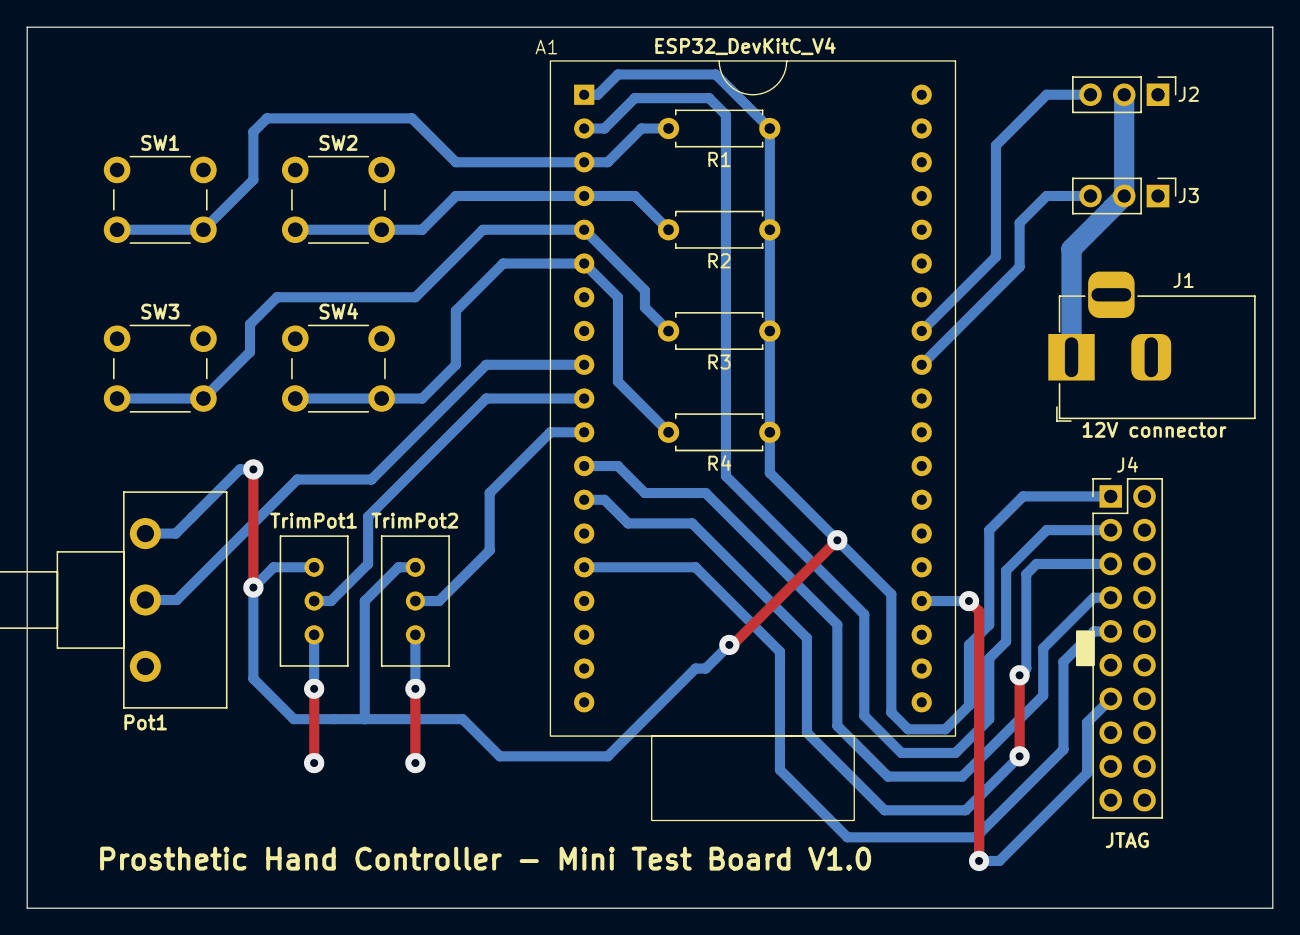
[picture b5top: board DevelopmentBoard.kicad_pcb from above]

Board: 2 copper layers, 93.7 x 66.3 mm, 16 parts (0 on the bottom side), 17 nets.
